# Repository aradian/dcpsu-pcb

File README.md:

# dcpsu-pcb
DCPSU - schematics and PCB layouts

### Card A:
- High efficiency
- Rough voltage output control
- Main use case is computer power supply
 
### Card B:
- Fine voltage output control
- Current limiting
- Main use case is benchtop lab power supply
 
### Backplane-testboard:
- Platform for card testing/development

### Component selection/design
- [Buck regulator DAC control](https://www.desmos.com/calculator/go5xqh90k3)
- [Buck regulator circuit attributes](https://www.desmos.com/calculator/a7n2unce4d)

### LICENSE
[CreativeCommons BY-SA](https://creativecommons.org/licenses/by-sa/4.0/)

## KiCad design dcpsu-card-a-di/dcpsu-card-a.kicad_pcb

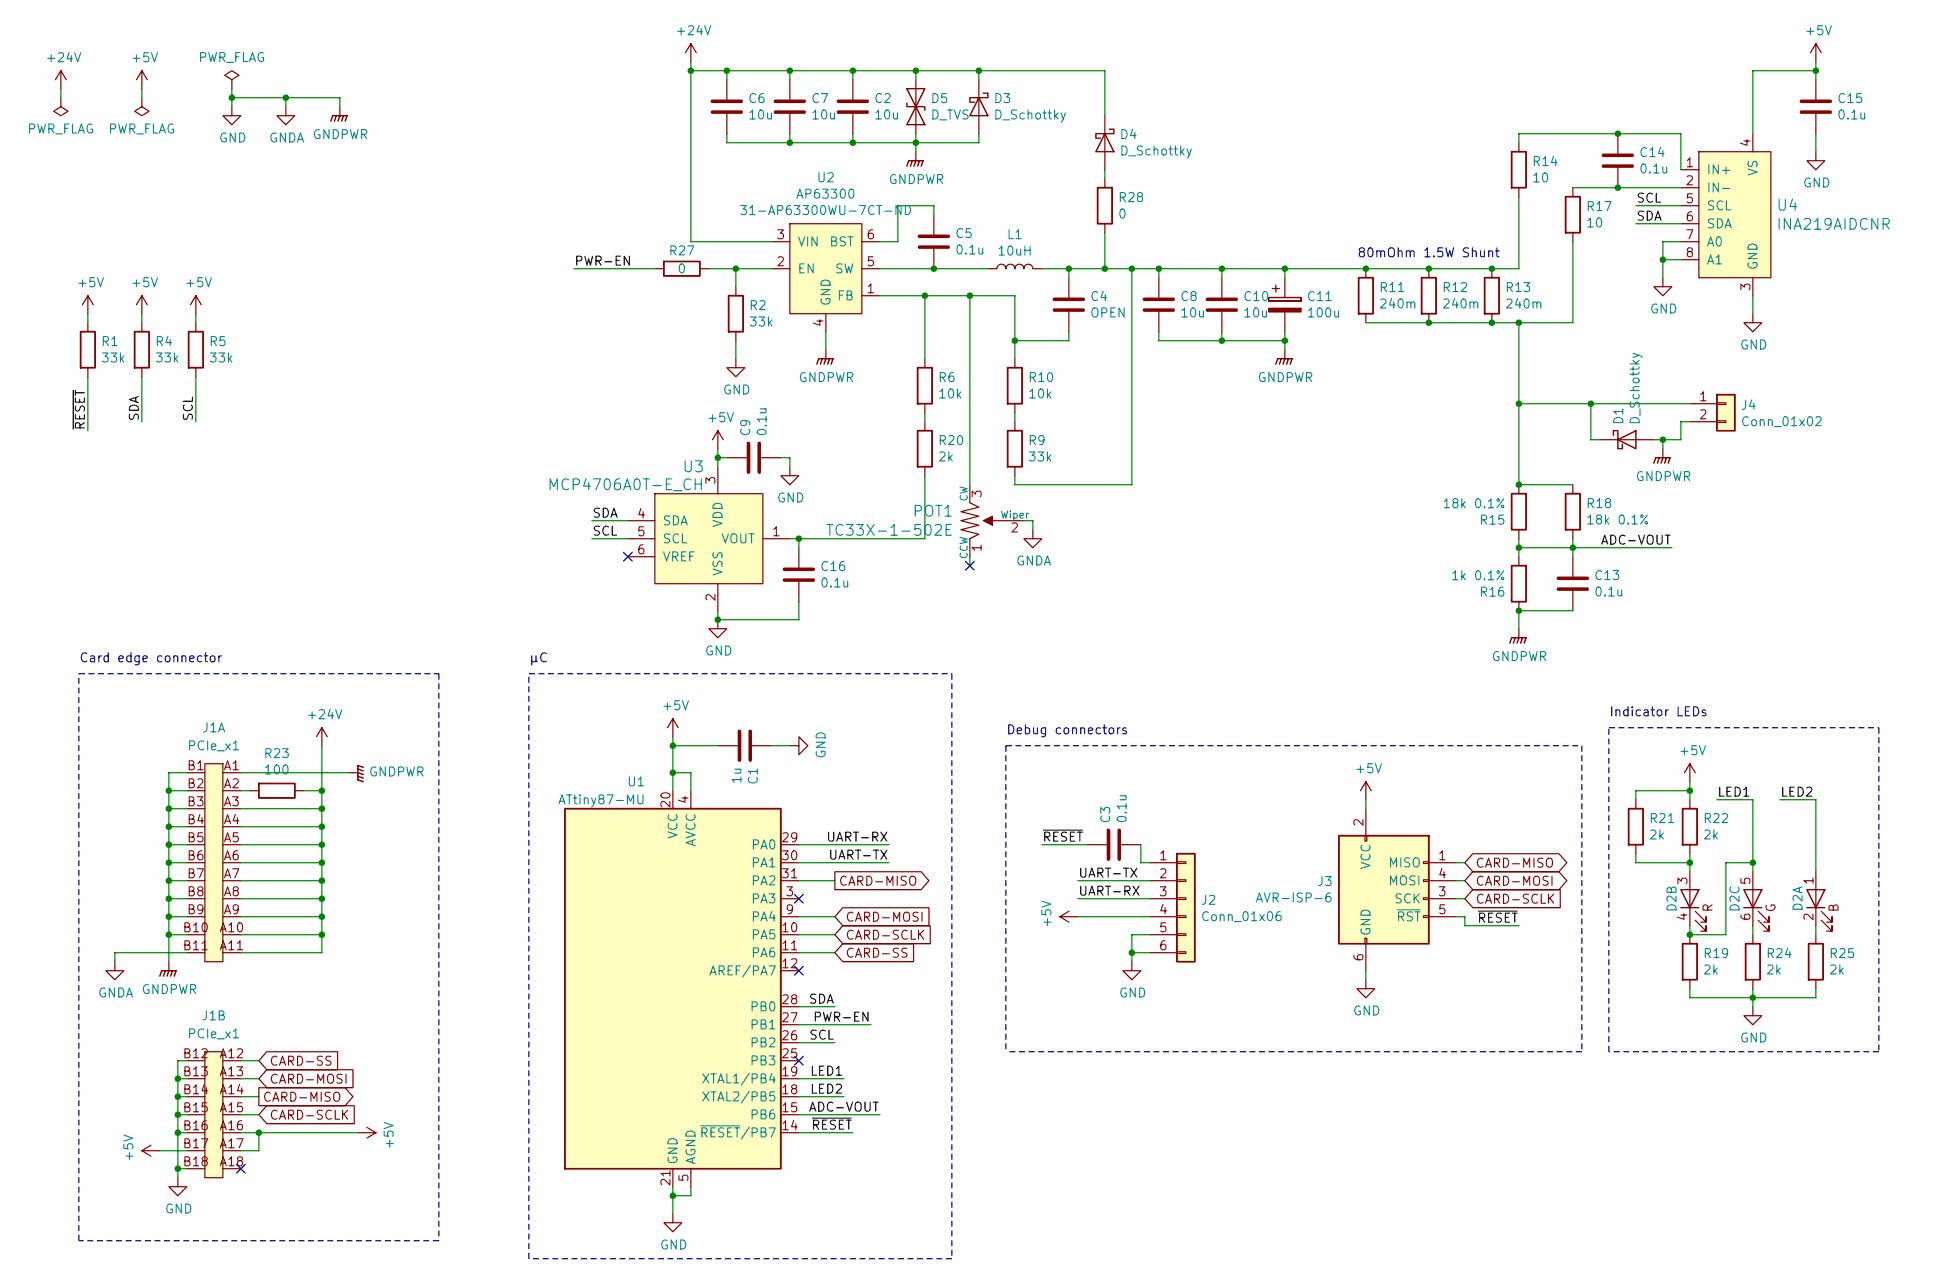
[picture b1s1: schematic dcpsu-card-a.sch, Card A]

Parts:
C1: 1u; C_0603_1608Metric_Pad1.05x0.95mm_HandSolder; Digi-Key_PN 399-7847-1-ND
C2, C7, C8, C10: 10u; C_1206_3216Metric_Pad1.42x1.75mm_HandSolder; Digi-Key_PN 1276-6736-1-ND
C3, C9, C13, C14, C15, C16: 0.1u; C_0603_1608Metric_Pad1.05x0.95mm_HandSolder; Digi-Key_PN 399-1099-1-ND
C4: OPEN; C_0603_1608Metric_Pad1.05x0.95mm_HandSolder
C5: 0.1u; C_0603_1608Metric_Pad1.05x0.95mm_HandSolder; Digi-Key_PN 1276-1000-1-ND
C6: 10u; C_0603_1608Metric_Pad1.05x0.95mm_HandSolder; Digi-Key_PN 1276-6736-1-ND
C11: 100u; CP_Elec_6.3x7.7; Digi-Key_PN 732-8511-1-ND
D1, D3, D4: D_Schottky; TO-277B-MBR860S; Digi-Key_PN 1655-2176-1-ND
D2: QLS6B-FKW; Digi-Key_PN QLS6B-FKW-CNSNSF043CT-ND
D5: D_TVS; D_0201_0603Metric; Digi-Key_PN ESD253B1W0201E6327XTSA1CT-ND
J1: PCIe_x1; BUS_PCIe_custom
J2: Conn_01x06; PinHeader_1x06_P2.54mm_Vertical
J3: AVR-ISP-6; IDC-Header_2x03_P2.54mm_Vertical; Digi-Key_PN 609-2845-ND
J4: Conn_01x02; Molex_Nano-Fit_105313-xx02_1x02_P2.50mm_Horizontal; Digi-Key_PN WM14972-ND
L1: 10uH; L_Pad4.05x4.4mm_LMLP1011; Digi-Key_PN 478-LMLP1011M100DTASCT-ND
POT1: TC33X-1-502E; Trimpot_3.8mmx3.6mm_TC33X-2-103E; MPN TC33X-1-502E; Digi-Key_PN TC33X-1-502ECT-ND
R1, R2, R4, R5, R9: 33k; R_0603_1608Metric_Pad1.05x0.95mm_HandSolder; Digi-Key_PN RMCF0603JT33K0CT-ND
R6, R10: 10k; R_0603_1608Metric_Pad1.05x0.95mm_HandSolder; Digi-Key_PN RMCF0603JT10K0CT-ND
R11, R12, R13: 240m; R_1206_3216Metric_Pad1.42x1.75mm_HandSolder; Digi-Key_PN 273-KDV12DR240ETCT-ND
R14, R17: 10; R_0603_1608Metric_Pad1.05x0.95mm_HandSolder; Digi-Key_PN YAG4486CT-ND
R15, R18: 18k 0.1%; R_0603_1608Metric_Pad1.05x0.95mm_HandSolder; Digi-Key_PN P20113CT-ND
R16: 1k 0.1%; R_0603_1608Metric_Pad1.05x0.95mm_HandSolder; Digi-Key_PN P19972CT-ND
R19, R20, R21, R22, R24, R25: 2k; R_0603_1608Metric_Pad1.05x0.95mm_HandSolder; Digi-Key_PN RMCF0603FT2K00CT-ND
R23: 100; R_0603_1608Metric_Pad1.05x0.95mm_HandSolder; Digi-Key_PN RMCF0603JT100RCT-ND
R27, R28: 0; R_1206_3216Metric_Pad1.42x1.75mm_HandSolder
U1: ATtiny87-MU; QFN-32-1EP_5x5mm_P0.5mm_EP3.1x3.1mm; Digi-Key_PN ATTINY87-MU-ND
U2: AP63300; SOT-23-6_Handsoldering; Digi-Key_PN 31-AP63300WU-7CT-ND
U3: MCP4706A0T-E_CH; SOT-23-6; MPN MCP4706A0T-E/CH; Digi-Key_PN MCP4706A0T-E/CHCT-ND
U4: INA219AIDCNR; SOT-23-8_Handsoldering; MPN INA219AIDCNR; Digi-Key_PN 296-23770-1-ND

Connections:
+5V: C1.2, C9.1, C15.1, J1.A16, J1.A17, J1.B17, J2.4, J3.2 (VCC), R1.1, R4.1, R5.1, R21.1, R22.1, U1.4 (AVCC), U1.20 (VCC), U3.3 (VDD), U4.4 (VS); also elsewhere on the board
+24V: C2.1, C6.1, C7.1, D3.1 (K), D4.1 (K), D5.1 (A1), J1.A3, J1.A4, J1.A5, J1.A6, J1.A7, J1.A8, J1.A9, J1.A10, J1.A11, R23.1, U2.3 (VIN)
/ADC-VOUT: C13.1, R15.1, R16.2, R18.2, U1.15 (PB6)
/LED1: D2.4 (R_K), D2.5 (G_A), R19.1, U1.19 (XTAL1/PB4)
/LED2: D2.1 (B_A), U1.18 (XTAL2/PB5)
/PWR-EN: R27.2, U1.27 (PB1)
/SCL: R5.2, U1.26 (PB2), U3.5 (SCL), U4.5 (SCL)
/SDA: R4.2, U1.28 (PB0), U3.4 (SDA), U4.6 (SDA)
/UART-RX: J2.3, U1.29 (PA0)
/UART-TX: J2.2, U1.30 (PA1)
/~RESET: C3.1, J3.5 (~RST), R1.2, U1.14 (~RESET~/PB7)
CARD-MISO: J1.A14, J3.1 (MISO), U1.31 (PA2)
CARD-MOSI: J1.A13, J3.4 (MOSI), U1.9 (PA4)
CARD-SCLK: J1.A15, J3.3 (SCK), U1.10 (PA5)
CARD-SS: J1.A12, U1.11 (PA6)
GND: C1.1, C2.2, C6.2, C7.2, C8.2, C9.2, C10.2, C11.2, C13.2, C15.2, C16.2, D1.2 (A), D3.2 (A), D5.2 (A2), J1.A1, J1.B1, J1.B2, J1.B3, J1.B4, J1.B5, J1.B6, J1.B7, J1.B8, J1.B9, J1.B10, J1.B11, J1.B12, J1.B13, J1.B14, J1.B15, J1.B16, J1.B18, J2.5, J2.6, J3.6 (GND), J4.2, POT1.2 (Wiper), R2.2, R16.1, R19.2, R24.2, R25.2, U1.5 (AGND), U1.21 (GND), U1.33 (GND), U2.4 (GND), U3.2 (VSS), U4.3 (GND), U4.7 (A0), U4.8 (A1); also elsewhere on the board
unnamed: C3.2, J2.1
unnamed: C4.2, POT1.3 (CW), R6.1, R10.1, U2.1 (FB)
unnamed: C5.1, U2.6 (BST)
unnamed: C5.2, L1.1, U2.5 (SW)
unnamed: C4.1, C8.1, C10.1, C11.1, L1.2, R9.2, R11.1, R12.1, R13.1, R14.2, R28.1
unnamed: C14.1, R14.1, U4.1 (IN+)
unnamed: C14.2, R17.1, U4.2 (IN-)
unnamed: C16.1, R20.2, U3.1 (VOUT)
unnamed: D1.1 (K), J4.1, R11.2, R12.2, R13.2, R15.2, R17.2, R18.1
unnamed: D2.2 (B_K), R25.1
unnamed: D2.3 (R_A), R21.2, R22.2
unnamed: D2.6 (G_K), R24.1
unnamed: D4.2 (A), R28.2
unnamed: J1.A2, R23.2
unnamed: R2.1, R27.1, U2.2 (EN)
unnamed: R9.1, R10.2
unnamed: R6.2, R20.1

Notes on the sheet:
80mOhm 1.5W Shunt
Indicator LEDs
Debug connectors
Card edge connector

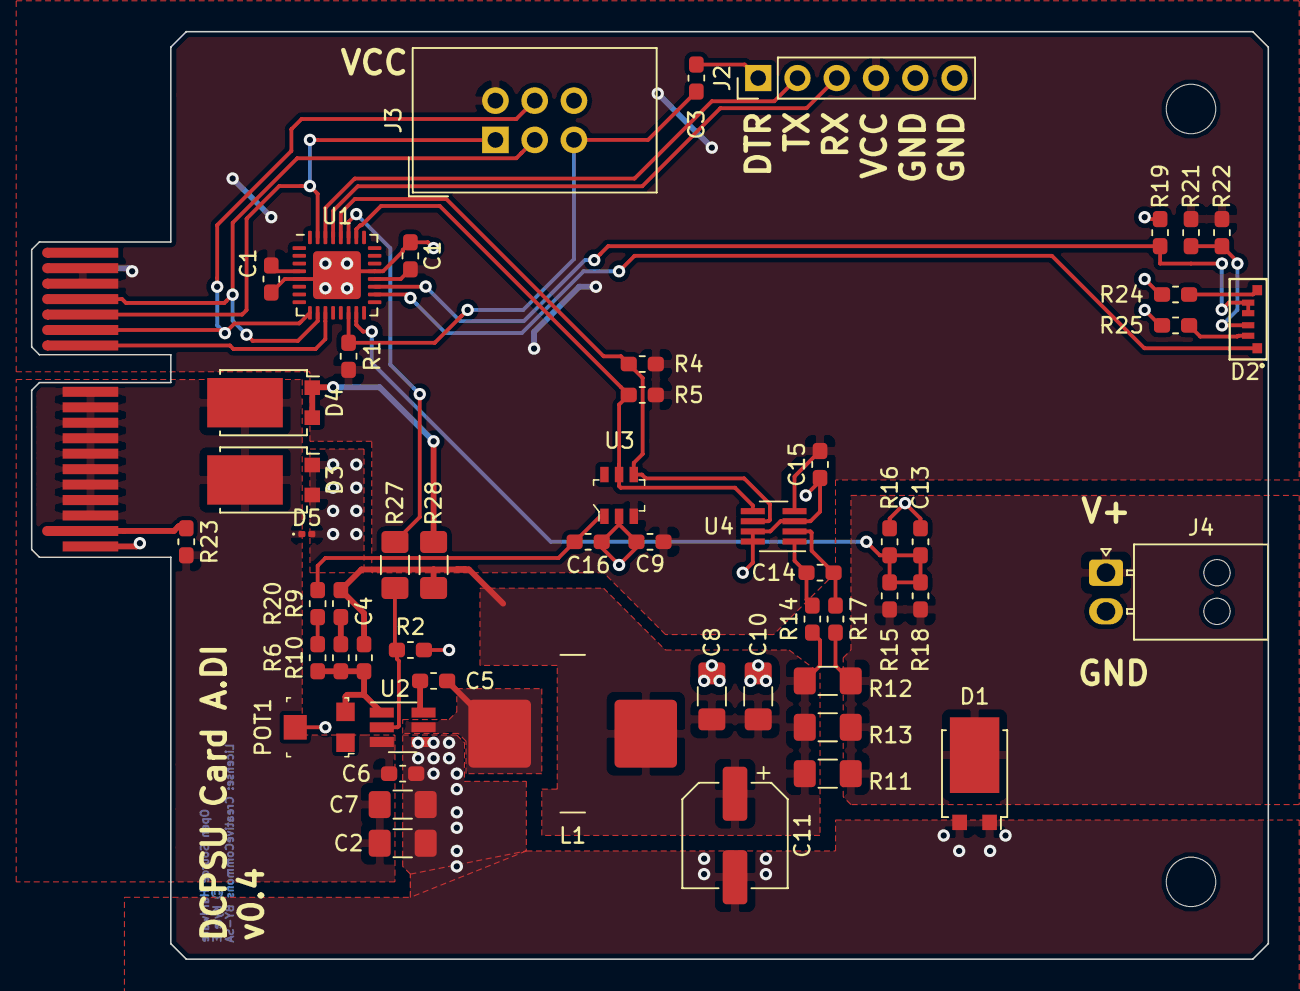
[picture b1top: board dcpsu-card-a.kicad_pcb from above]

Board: 2 copper layers, 80.0 x 60.0 mm, 55 parts (1 on the bottom side), 33 nets.

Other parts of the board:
C1#2: C_0603_1608Metric_Pad1.05x0.95mm_HandSolder

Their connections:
+5V: C1#2.2; also elsewhere on the board
GND: C1#2.1; also elsewhere on the board

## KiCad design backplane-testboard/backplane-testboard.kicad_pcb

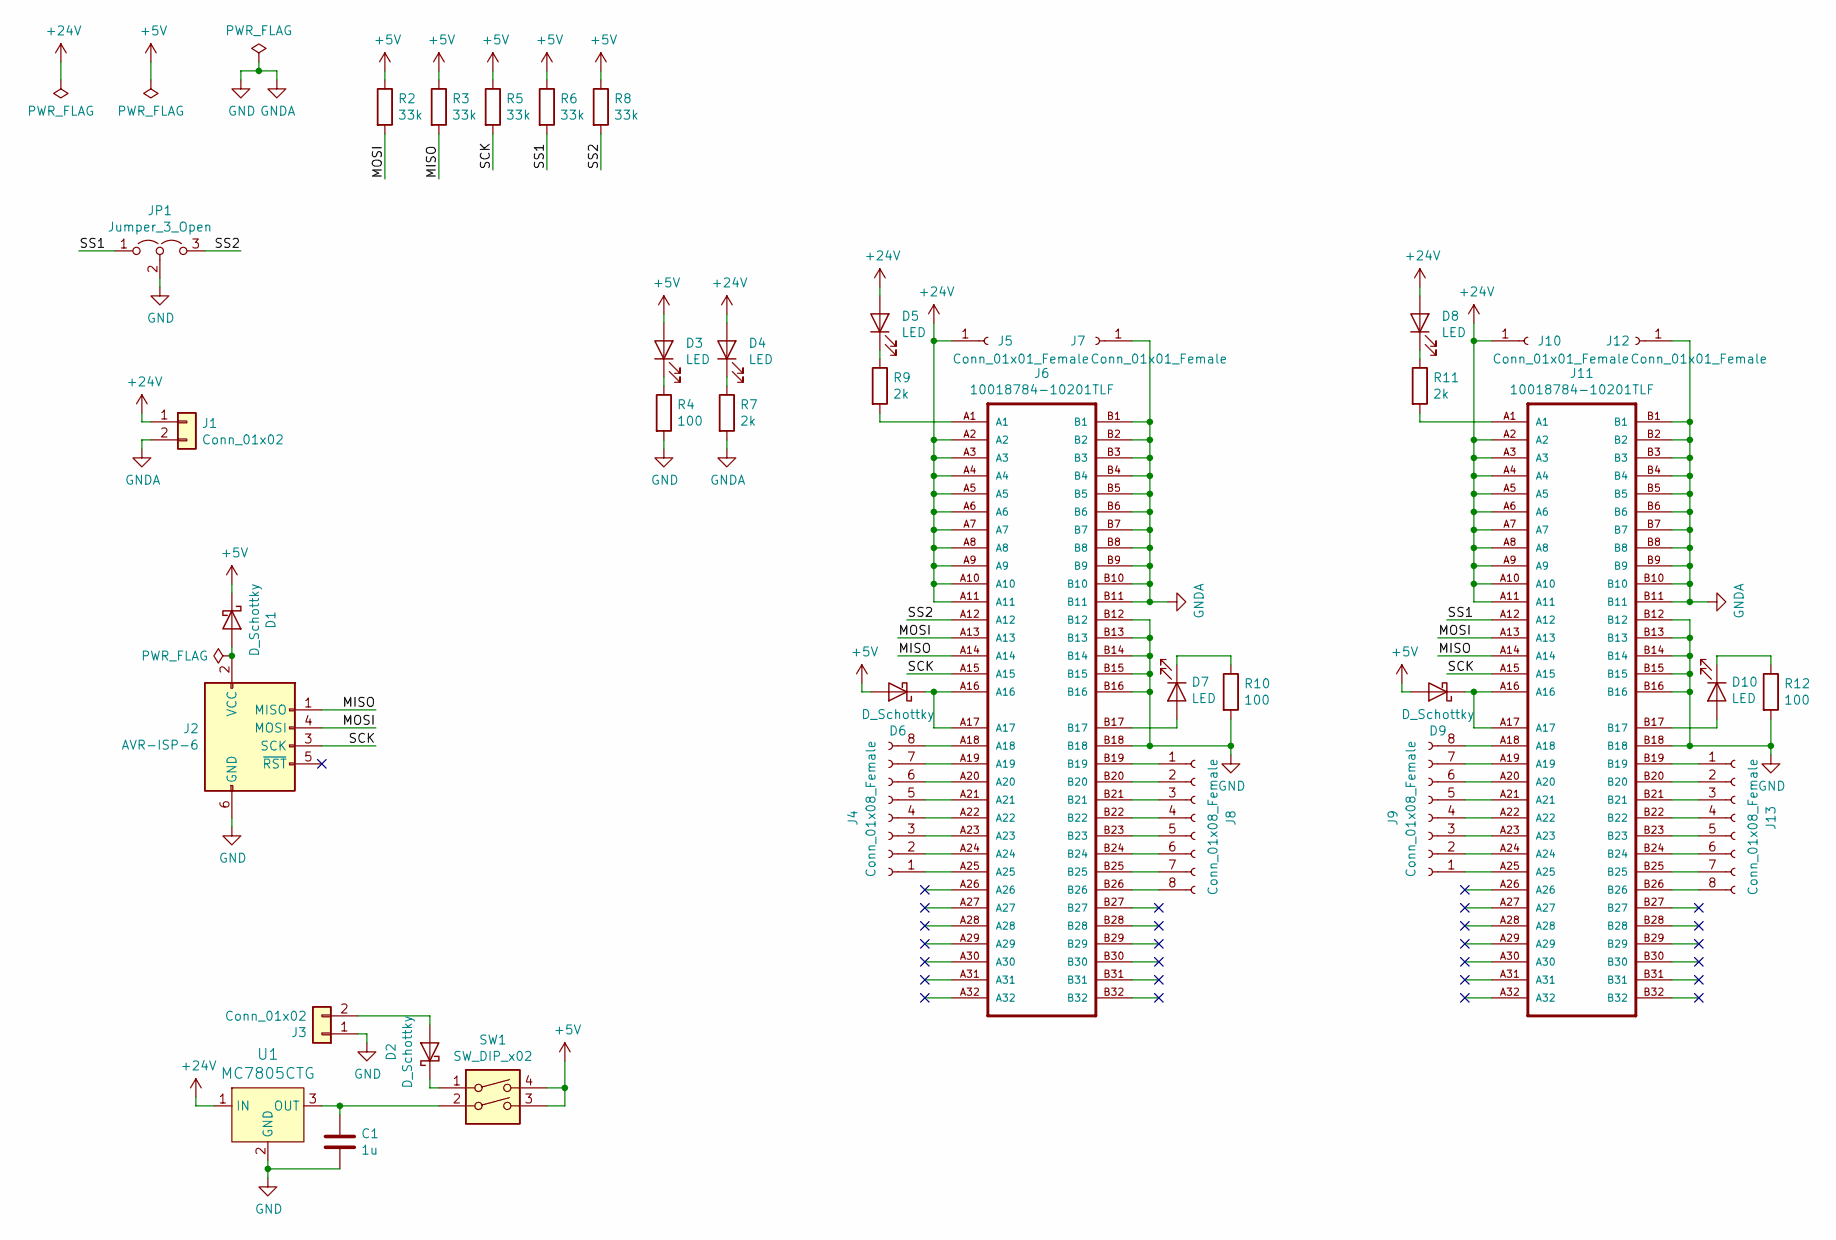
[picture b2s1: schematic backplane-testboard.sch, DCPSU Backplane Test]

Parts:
C1: 1u; C_0603_1608Metric_Pad1.05x0.95mm_HandSolder; Digi-Key_PN 399-7847-1-ND
D1, D6, D9: D_Schottky; D_SOD-123F; Digi-Key_PN 1655-1928-1-ND
D2: D_Schottky; D_SOD-123F
D3, D4, D5, D7, D8, D10: LED; LED_0603; Digi-Key_PN 732-4971-1-ND
J1: Conn_01x02; Molex_Mini-Fit_Jr_5566-02A_2x01_P4.20mm_Vertical; Digi-Key_PN WM3800-ND
J2: AVR-ISP-6; IDC-Header_2x03_P2.54mm_Vertical; Digi-Key_PN 609-2845-ND
J3: Conn_01x02; PinHeader_1x02_P2.54mm_Vertical
J4, J8, J9, J13: Conn_01x08_Female; PinSocket_1x08_P2.54mm_Vertical; Digi-Key_PN 1212-1097-ND
J5, J7, J10, J12: Conn_01x01_Female; SolderWirePad_1x01_Drill1.5mm
J6, J11: 10018784-10201TLF; CONN_10018784-10201TLF; Digi-Key_PN 609-2026-ND
JP1: Jumper_3_Open; PinHeader_1x03_P2.54mm_Vertical
R2, R3, R5, R6, R8: 33k; R_0603_1608Metric_Pad1.05x0.95mm_HandSolder; Digi-Key_PN RMCF0603JT33K0CT-ND
R4, R10, R12: 100; R_0603_1608Metric_Pad1.05x0.95mm_HandSolder; Digi-Key_PN RMCF0603JT100RCT-ND
R7, R9, R11: 2k; R_0603_1608Metric_Pad1.05x0.95mm_HandSolder; Digi-Key_PN RMCF0603JT2K00CT-ND
SW1: SW_DIP_x02; DIP-4_W7.62mm; Digi-Key_PN J577-ND
U1: MC7805CTG; TO-220-3; MPN MC7805CTG; Digi-Key_PN MC7805CTGOS-ND

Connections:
+5V: D1.1 (K), D3.2 (A), D6.2 (A), D9.2 (A), R2.1, R3.1, R5.1, R6.1, R8.1, SW1.3, SW1.4
+24V: D4.2 (A), D5.2 (A), D8.2 (A), J1.1, J5.1, J6.A2, J6.A3, J6.A4, J6.A5, J6.A6, J6.A7, J6.A8, J6.A9, J6.A10, J6.A11, J10.1, J11.A2, J11.A3, J11.A4, J11.A5, J11.A6, J11.A7, J11.A8, J11.A9, J11.A10, J11.A11, U1.1 (IN)
/MISO: J2.1 (MISO), J6.A14, J11.A14, R3.2
/MOSI: J2.4 (MOSI), J6.A13, J11.A13, R2.2
/SCK: J2.3 (SCK), J6.A15, J11.A15, R5.2
/SS1: J11.A12, JP1.1 (A), R6.2
/SS2: J6.A12, JP1.3 (B), R8.2
GND: C1.2, J1.2, J2.6 (GND), J3.1, J6.B1, J6.B2, J6.B3, J6.B4, J6.B5, J6.B6, J6.B7, J6.B8, J6.B9, J6.B10, J6.B11, J6.B12, J6.B13, J6.B14, J6.B15, J6.B16, J6.B18, J7.1, J11.B1, J11.B2, J11.B3, J11.B4, J11.B5, J11.B6, J11.B7, J11.B8, J11.B9, J11.B10, J11.B11, J11.B12, J11.B13, J11.B14, J11.B15, J11.B16, J11.B18, J12.1, JP1.2 (C), R4.2, R7.2, R10.2, R12.2, U1.2 (GND)
unnamed: C1.1, SW1.2, U1.3 (OUT)
unnamed: D1.2 (A), J2.2 (VCC)
unnamed: D2.1 (K), SW1.1
unnamed: D2.2 (A), J3.2
unnamed: D3.1 (K), R4.1
unnamed: D4.1 (K), R7.1
unnamed: D5.1 (K), R9.1
unnamed: D6.1 (K), J6.A16, J6.A17
unnamed: D7.1 (K), R10.1
unnamed: D7.2 (A), J6.B17
unnamed: D8.1 (K), R11.1
unnamed: D9.1 (K), J11.A16, J11.A17
unnamed: D10.1 (K), R12.1
unnamed: D10.2 (A), J11.B17
unnamed: J4.1, J6.A25
unnamed: J4.2, J6.A24
unnamed: J4.3, J6.A23
unnamed: J4.4, J6.A22
unnamed: J4.5, J6.A21
unnamed: J4.6, J6.A20
unnamed: J4.7, J6.A19
unnamed: J4.8, J6.A18
unnamed: J6.A1, R9.2
unnamed: J6.B19, J8.1
unnamed: J6.B20, J8.2
unnamed: J6.B21, J8.3
unnamed: J6.B22, J8.4
unnamed: J6.B23, J8.5
unnamed: J6.B24, J8.6
unnamed: J6.B25, J8.7
unnamed: J6.B26, J8.8
unnamed: J11.A1, R11.2
unnamed: J9.8, J11.A18
unnamed: J9.7, J11.A19
unnamed: J9.6, J11.A20
unnamed: J9.5, J11.A21
unnamed: J9.4, J11.A22
unnamed: J9.3, J11.A23
unnamed: J9.2, J11.A24
unnamed: J9.1, J11.A25
unnamed: J11.B19, J13.1
unnamed: J11.B20, J13.2
unnamed: J11.B21, J13.3
unnamed: J11.B22, J13.4
unnamed: J11.B23, J13.5
unnamed: J11.B24, J13.6
unnamed: J11.B25, J13.7
unnamed: J11.B26, J13.8

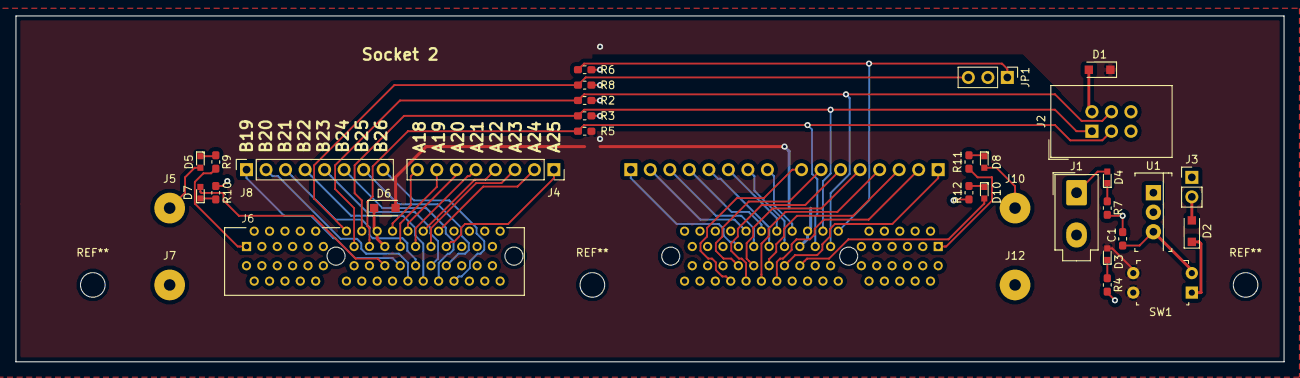
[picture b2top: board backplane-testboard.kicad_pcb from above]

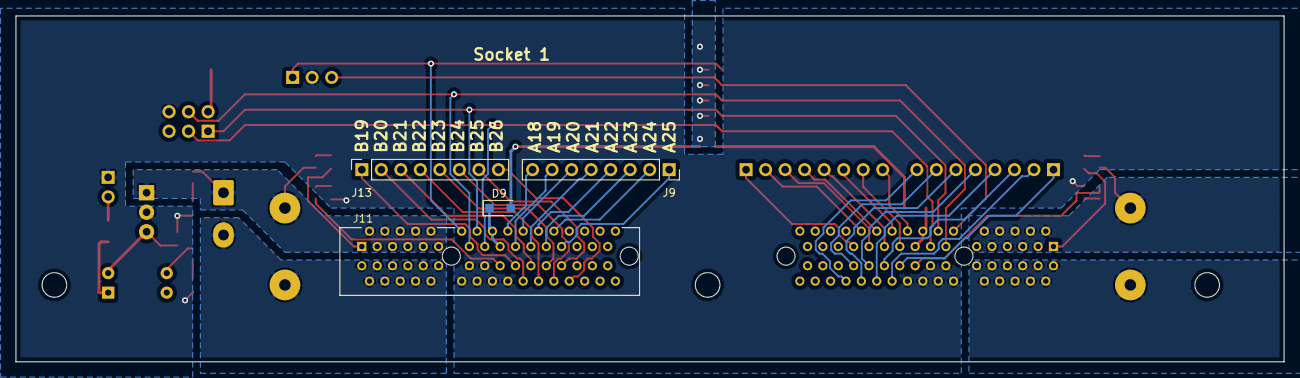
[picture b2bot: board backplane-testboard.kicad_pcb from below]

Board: 2 copper layers, 165.0 x 45.0 mm, 38 parts (4 on the bottom side), 56 nets.

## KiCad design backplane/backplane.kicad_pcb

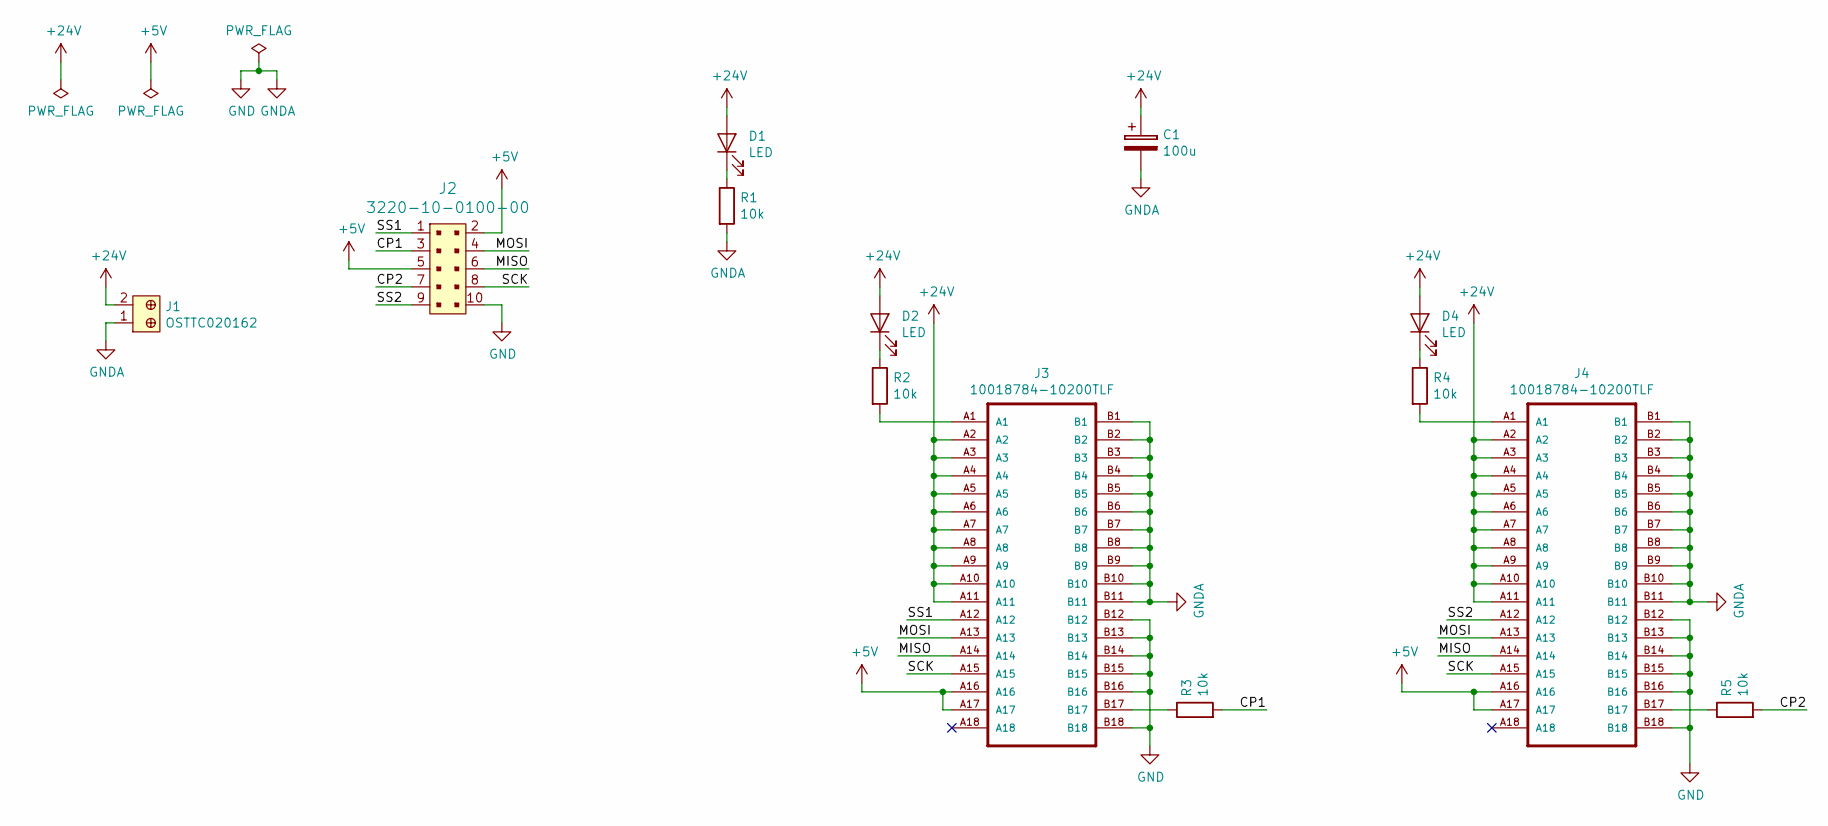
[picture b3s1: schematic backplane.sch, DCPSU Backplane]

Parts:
C1: 100u; CP_Elec_6.3x7.7; Digi-Key_PN 565-2234-1-ND
D1, D2, D4: LED; LED_0603; Digi-Key_PN 732-4971-1-ND
J1: OSTTC020162; Term_Block_1x2_P5mm; MPN OSTTC020162; Digi-Key_PN ED2600-ND
J2: 3220-10-0100-00; PinHeader_2x5_P1.27mm_Drill.7mm; MPN 3220-10-0100-00; Digi-Key_PN 1175-1627-ND
J3, J4: 10018784-10200TLF; Digi-Key_PN 609-2025-ND
R1, R2, R3, R4, R5: 10k; R_0603_1608Metric_Pad1.05x0.95mm_HandSolder; Digi-Key_PN RMCF0603JT10K0CT-ND

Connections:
+5V: J2.2, J2.5, J3.A16, J3.A17, J4.A16, J4.A17
+24V: C1.1, D1.2 (A), D2.2 (A), D4.2 (A), J1.2, J3.A2, J3.A3, J3.A4, J3.A5, J3.A6, J3.A7, J3.A8, J3.A9, J3.A10, J3.A11, J4.A2, J4.A3, J4.A4, J4.A5, J4.A6, J4.A7, J4.A8, J4.A9, J4.A10, J4.A11
/CP1: J2.3, R3.2
/CP2: J2.7, R5.2
/MISO: J2.6, J3.A14, J4.A14
/MOSI: J2.4, J3.A13, J4.A13
/SCK: J2.8, J3.A15, J4.A15
/SS1: J2.1, J3.A12
/SS2: J2.9, J4.A12
GND: C1.2, J1.1, J2.10, J3.B1, J3.B2, J3.B3, J3.B4, J3.B5, J3.B6, J3.B7, J3.B8, J3.B9, J3.B10, J3.B11, J3.B12, J3.B13, J3.B14, J3.B15, J3.B16, J3.B18, J4.B1, J4.B2, J4.B3, J4.B4, J4.B5, J4.B6, J4.B7, J4.B8, J4.B9, J4.B10, J4.B11, J4.B12, J4.B13, J4.B14, J4.B15, J4.B16, J4.B18, R1.2
unnamed: D1.1 (K), R1.1
unnamed: D2.1 (K), R2.1
unnamed: D4.1 (K), R4.1
unnamed: J3.A1, R2.2
unnamed: J3.B17, R3.1
unnamed: J4.A1, R4.2
unnamed: J4.B17, R5.1

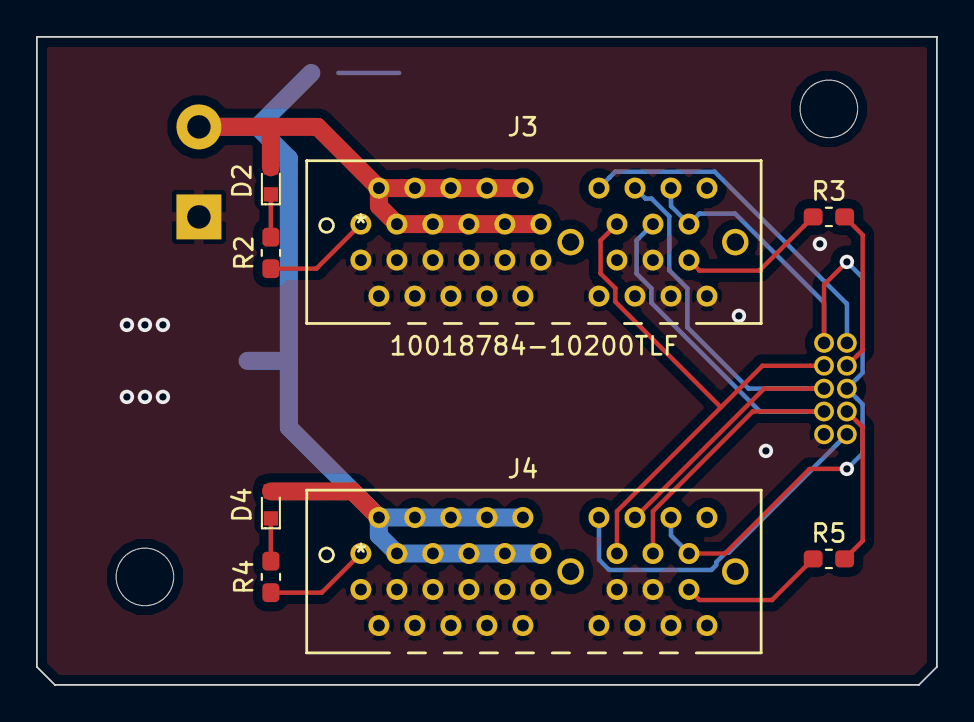
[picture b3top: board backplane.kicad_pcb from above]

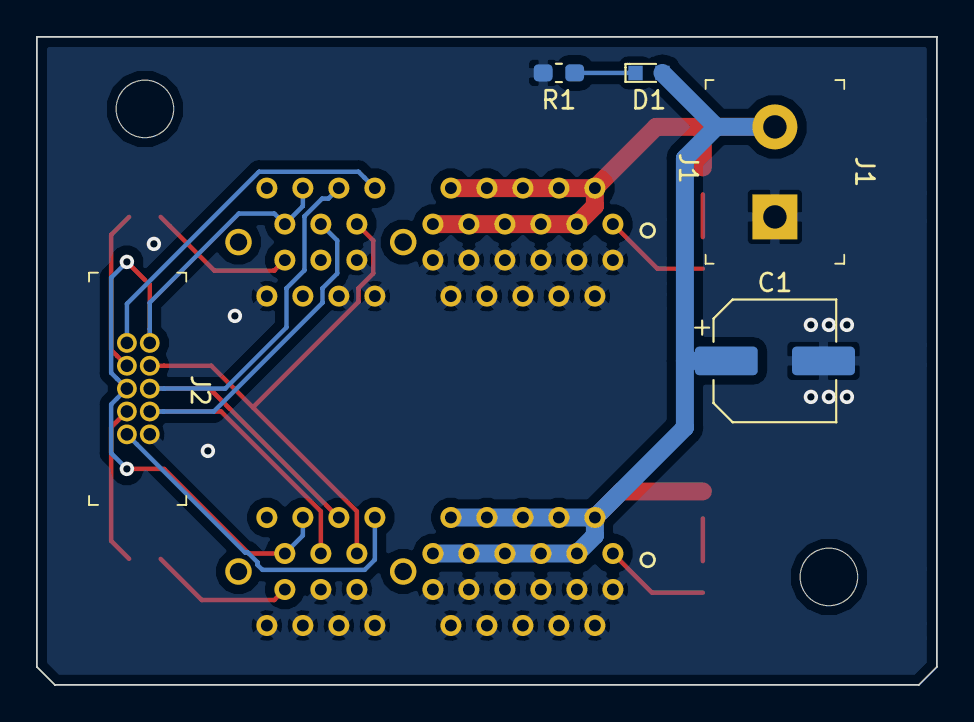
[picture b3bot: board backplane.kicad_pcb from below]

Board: 2 copper layers, 50.0 x 36.0 mm, 13 parts (5 on the bottom side), 17 nets.

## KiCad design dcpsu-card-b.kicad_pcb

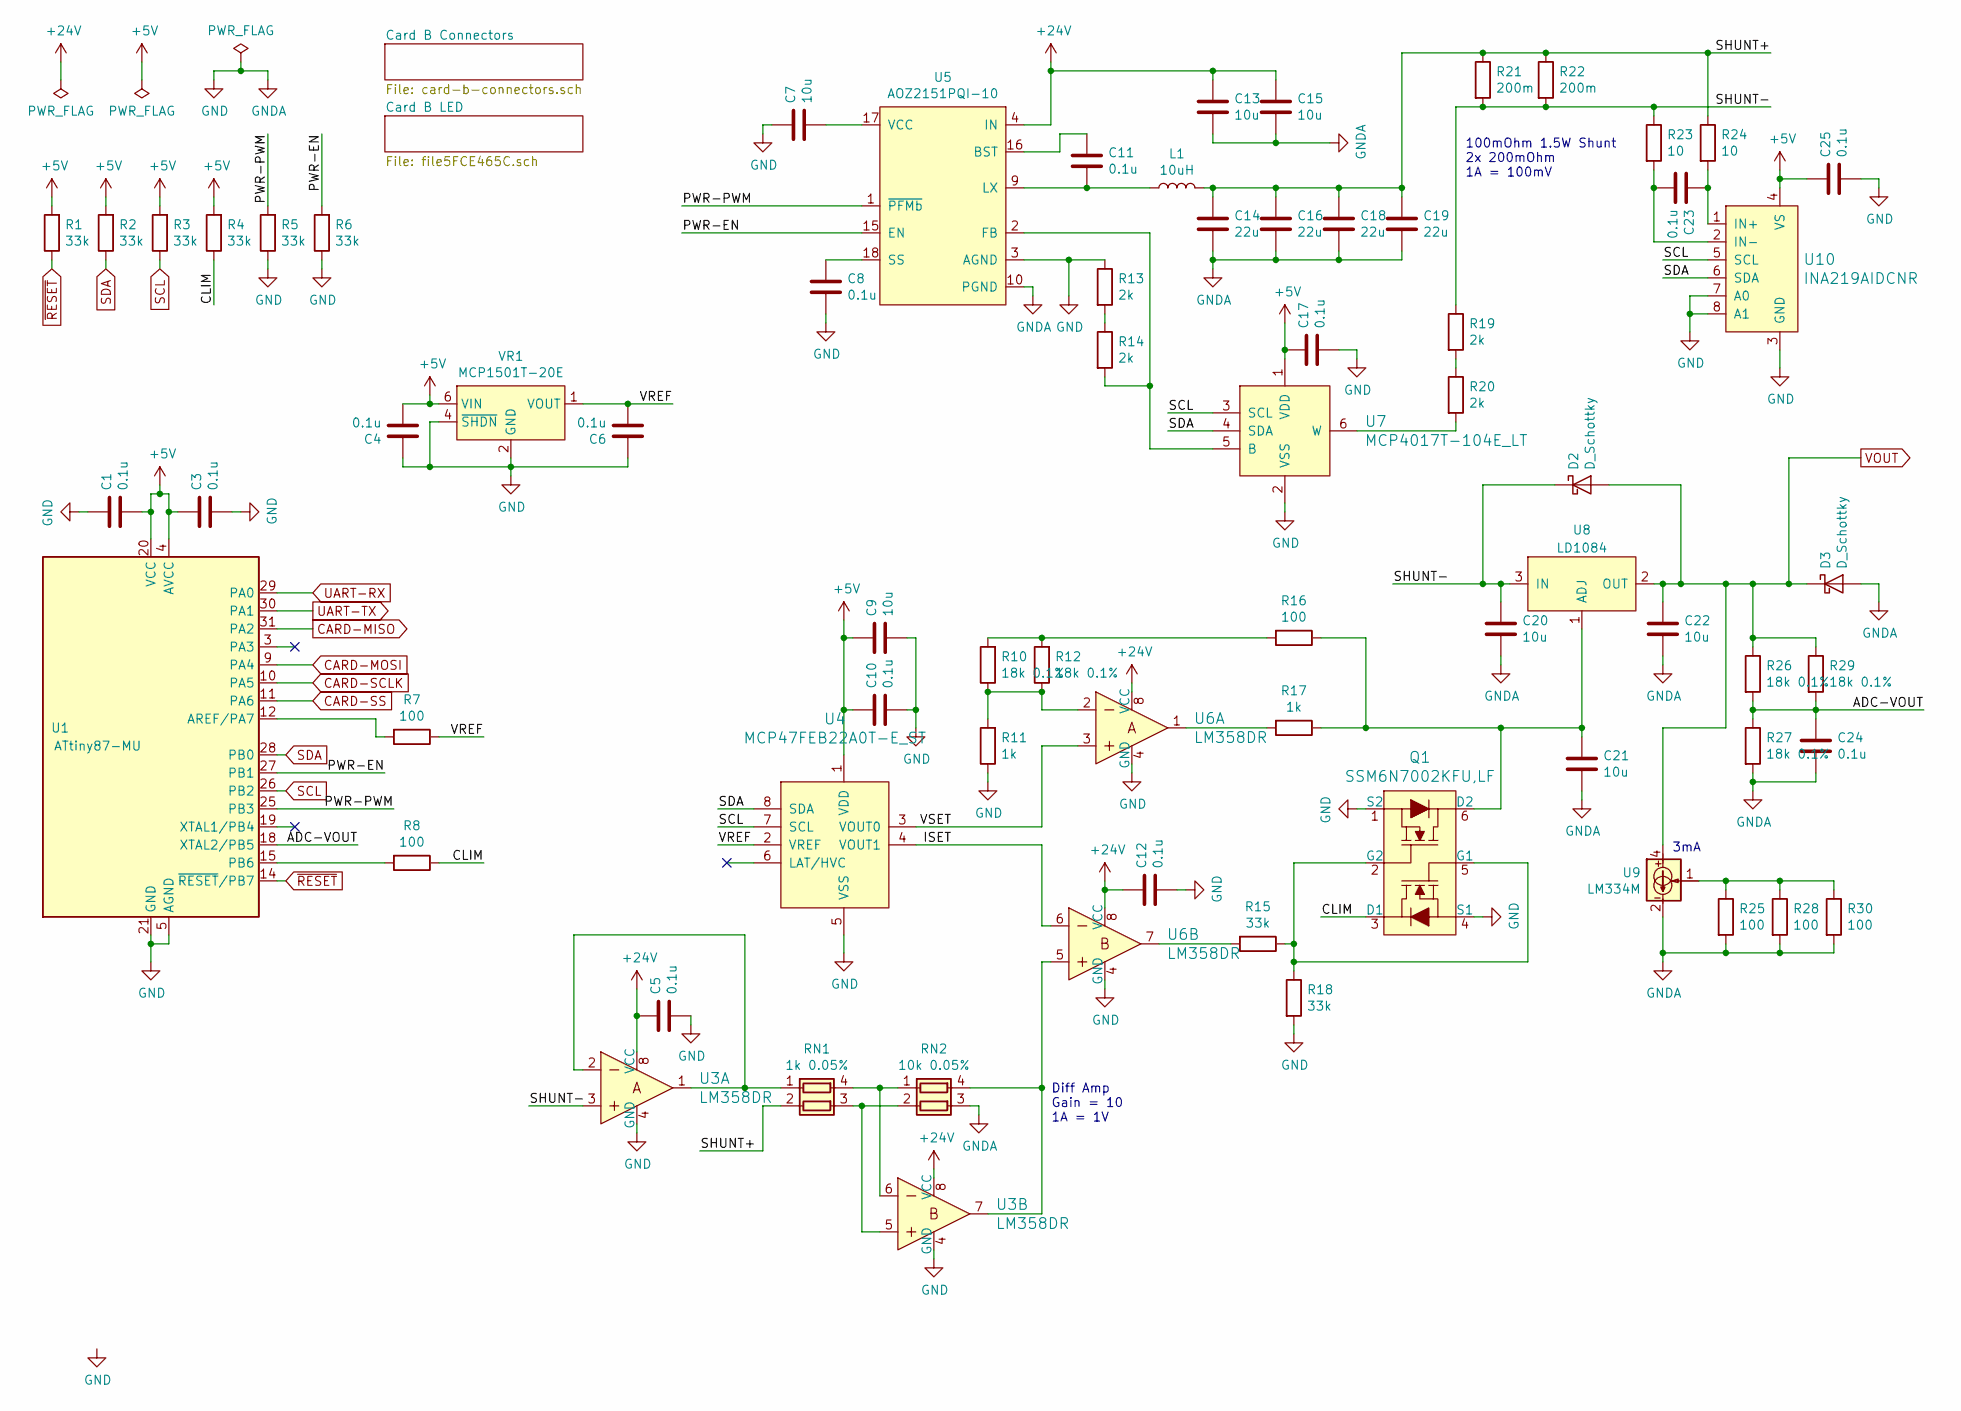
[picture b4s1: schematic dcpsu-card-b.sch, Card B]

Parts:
C1, C3, C4, C5, C6, C10, C12, C17, C23, C24, C25: 0.1u; C_0603_1608Metric_Pad1.05x0.95mm_HandSolder; Digi-Key_PN 399-1099-1-ND
C7: 10u; C_0603_1608Metric_Pad1.05x0.95mm_HandSolder; Digi-Key_PN 478-10766-1-ND
C8, C11: 0.1u; C_0603_1608Metric_Pad1.05x0.95mm_HandSolder; Digi-Key_PN 1276-1000-1-ND
C9, C13, C15, C20, C21, C22: 10u; C_1206_3216Metric_Pad1.42x1.75mm_HandSolder; Digi-Key_PN 1276-6736-1-ND
C14, C16, C18, C19: 22u; C_1206_3216Metric_Pad1.42x1.75mm_HandSolder; Digi-Key_PN 1276-3047-1-ND
D2, D3: D_Schottky; TO-277B-MBR860S; Digi-Key_PN 1655-2176-1-ND
L1: 10uH; L_Pad4.05x4.4mm_LMLP1011; Digi-Key_PN 478-LMLP1011M100DTASCT-ND
Q1: SSM6N7002KFU,LF; SOT-363; MPN 2N7002DW-7-F; Digi-Key_PN 2N7002DW-FDICT-ND
R1, R2, R3, R4, R5, R6, R15, R18: 33k; R_0603_1608Metric_Pad1.05x0.95mm_HandSolder; Digi-Key_PN RMCF0603JT33K0CT-ND
R7, R8, R16, R25, R28, R30: 100; R_0603_1608Metric_Pad1.05x0.95mm_HandSolder; Digi-Key_PN RMCF0603JT100RCT-ND
R10, R12, R26, R27, R29: 18k 0.1%; R_0603_1608Metric_Pad1.05x0.95mm_HandSolder; Digi-Key_PN P20113CT-ND
R11, R17: 1k; R_0603_1608Metric_Pad1.05x0.95mm_HandSolder; Digi-Key_PN P19972CT-ND
R13, R14, R19, R20: 2k; R_0603_1608Metric_Pad1.05x0.95mm_HandSolder; Digi-Key_PN RMCF0603FT2K00CT-ND
R21, R22: 200m; R_1206_3216Metric_Pad1.42x1.75mm_HandSolder; Digi-Key_PN 273-KDV12DR200ETCT-ND
R23, R24: 10; R_0603_1608Metric_Pad1.05x0.95mm_HandSolder; Digi-Key_PN RMCF0603FT10R0CT-ND
RN1: 1k 0.05%; R_Array_Convex_2x0606; Digi-Key_PN 749-1042-1-ND
RN2: 10k 0.05%; R_Array_Convex_2x0606; Digi-Key_PN 749-1046-1-ND
U1: ATtiny87-MU; QFN-32-1EP_5x5mm_P0.5mm_EP3.1x3.1mm; Digi-Key_PN ATTINY87-MU-ND
U3, U6: LM358DR; SOIC-8_W3.9mm; MPN LM358DR; Digi-Key_PN 296-1014-1-ND
U4: MCP47FEB22A0T-E_ST; TSSOP-8_W4.4mm; MPN MCP47FEB22A0-E/ST; Digi-Key_PN MCP47FEB22A0-E/ST-ND
U5: AOZ2151PQI-10; QFN-20-2EP_3x3mm_AOZ2151PQI-10; Digi-Key_PN 785-1866-1-ND
U7: MCP4017T-104E_LT; SOT-363; MPN MCP4017T-104E/LT; Digi-Key_PN MCP4017T-104E/LTCT-ND
U8: LD1084; TO-220-3_Vertical; Digi-Key_PN 497-3413-5-ND
U9: LM334M; SOIC-8_3.9x4.9mm_P1.27mm; Digi-Key_PN LM334MX/NOPBCT-ND
U10: INA219AIDCNR; SOT-23-8_Handsoldering; MPN INA219AIDCNR; Digi-Key_PN 296-23770-1-ND
VR1: MCP1501T-20E; SOT-23-6; MPN MCP1501T-20E/CHY; Digi-Key_PN MCP1501T-20E/CHYCT-ND

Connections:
+5V: C1.2, C3.1, C4.2, C9.1, C10.1, C17.1, C25.1, R1.2, R2.2, R3.2, R4.2, U1.4 (AVCC), U1.20 (VCC), U4.1 (VDD), U7.1 (VDD), U10.4 (VS), VR1.6 (VIN); also elsewhere on the board
+24V: C5.1, C12.1, C13.1, C15.1, U3.8 (VCC), U5.4 (IN), U5.5 (IN), U5.6 (IN), U5.7 (IN), U5.8 (IN), U6.8 (VCC); also elsewhere on the board
/ADC-VOUT: C24.1, R26.2, R27.1, R29.2, U1.18 (XTAL2/PB5)
/CLIM: Q1.3 (D1), R4.1, R8.1
/ISET: U4.4 (VOUT1), U6.6
/PWR-EN: R6.2, U1.27 (PB1), U5.15 (EN)
/PWR-PWM: R5.2, U1.25 (PB3), U5.1 (~PFMb)
/SHUNT+: C14.1, C16.1, C18.1, C19.1, L1.2, R21.1, R22.1, R24.1, RN1.2 (R2.1)
/SHUNT-: C20.1, D2.1 (K), R19.1, R21.2, R22.2, R23.1, U3.3, U8.3 (IN)
/VREF: C6.2, R7.1, U4.2 (VREF), VR1.1 (VOUT)
/VSET: U4.3 (VOUT0), U6.3
CARD-MISO: U1.31 (PA2); also elsewhere on the board
CARD-MOSI: U1.9 (PA4); also elsewhere on the board
CARD-SCLK: U1.10 (PA5); also elsewhere on the board
CARD-SS: U1.11 (PA6); also elsewhere on the board
GND: C1.1, C3.2, C4.1, C5.2, C6.1, C7.1, C8.2, C9.2, C10.2, C12.2, C13.2, C14.2, C15.2, C16.2, C17.2, C18.2, C19.2, C20.2, C21.2, C22.2, C24.2, C25.2, D3.2 (A), Q1.1 (S2), Q1.4 (S1), R5.1, R6.1, R11.1, R13.1, R18.2, R25.2, R27.2, R28.2, R30.2, RN2.3 (R2.2), U1.5 (AGND), U1.21 (GND), U1.33 (GND), U3.4 (GND), U4.5 (VSS), U5.3 (AGND), U5.10 (PGND), U5.11 (PGND), U5.12 (PGND), U6.4 (GND), U7.2 (VSS), U9.2, U9.3, U9.6, U9.7, U10.3 (GND), U10.7 (A0), U10.8 (A1), VR1.2 (GND), VR1.3 (GND), VR1.4 (~SHDN), VR1.5 (GND); also elsewhere on the board
unnamed 16: C7.2, U5.17 (VCC); also elsewhere on the board
unnamed: C8.1, U5.18 (SS)
unnamed: C11.1, U5.16 (BST)
unnamed: C11.2, L1.1, U5.9 (LX), U5.13 (LX), U5.14 (LX)
unnamed: C21.1, Q1.6 (D2), R16.1, R17.1, U8.1 (ADJ)
unnamed: C23.1, R24.2, U10.1 (IN+)
unnamed: C23.2, R23.2, U10.2 (IN-)
unnamed: Q1.2 (G2), Q1.5 (G1), R15.1, R18.1
unnamed: R7.2, U1.12 (AREF/PA7)
unnamed: R8.2, U1.15 (PB6)
unnamed: R10.1, R11.2, R12.1, U6.2
unnamed: R10.2, R12.2, R16.2
unnamed: R13.2, R14.1
unnamed: R14.2, U5.2 (FB), U7.5 (B)
unnamed: R15.2, U6.7
unnamed: R17.2, U6.1
unnamed: R19.2, R20.1
unnamed: R20.2, U7.6 (W)
unnamed: R25.1, R28.1, R30.1, U9.1
unnamed: RN1.1 (R1.1), U3.1, U3.2
unnamed: RN1.3 (R2.2), RN2.2 (R2.1), U3.5
unnamed: RN1.4 (R1.2), RN2.1 (R1.1), U3.6
unnamed: RN2.4 (R1.2), U3.7, U6.5
SCL: R3.1, U1.26 (PB2), U4.7 (SCL), U7.3 (SCL), U10.5 (SCL); also elsewhere on the board
SDA: R2.1, U1.28 (PB0), U4.8 (SDA), U7.4 (SDA), U10.6 (SDA); also elsewhere on the board
UART-RX: U1.29 (PA0); also elsewhere on the board
UART-TX: U1.30 (PA1); also elsewhere on the board
VOUT: C22.1, D2.2 (A), D3.1 (K), R26.1, R29.1, U8.2 (OUT), U9.4; also elsewhere on the board
~RESET: R1.1, U1.14 (~RESET~/PB7); also elsewhere on the board

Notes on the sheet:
100mOhm 1.5W Shunt 2x 200mOhm 1A = 100mV
3mA
Diff Amp Gain = 10 1A = 1V

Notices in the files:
dcpsu-card-a-ao/dcpsu-card-a.sch:
License: CC BY-SA
dcpsu-card-a-di/dcpsu-card-a.kicad_pcb:
© Kyle E
parts and their libraries:
Copyright 2016 Accelerated Designs. All rights reserved.
